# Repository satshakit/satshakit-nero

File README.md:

<h1 style="font-family: courier;" align="center"> satshakit-nero</h1>
<p align="center">

<div align="center"><i>An improved & fabbable multi-mcu flight controller board.</i></div>
</p>  

What is satshakit?
--

satshakit is a **Arduino IDE  and libraries compatible**, fabbable and open source board.

Here you can find all of the satshakit boards: **[satshakit organization](https://github.com/satshakit)**.

satshakit-nero
--

**satshakit-nero** is microcontroller board designed around the **ATMega1284P** and the **ATMega328P** chips and it is suitable for advanced drone applications and scenarios in which it is needed to have two available microcontrollers. The ATMega328P manages the flight with the **[Multiwii](http://www.multiwii.com/)** while the ATMega1284P can be used to inject and override the transmitter stick values (ROLL, PITCH, YAW and THROTTLE) or to manage a set of additional sensors. In the board there is a jumper to enable or disable the serial communication between the two microcontrollers (SERIAL_COMMON in the Eagle board).

The ATMega328P microntroller gives to this board all the features of the original **[satshakit flight controller board](https://github.com/satshakit/satshakit-flight-controller)**:

- support for [any drone configuration](http://www.multiwii.com/connecting-elements) up to **8 motors**
- support for up to **6 channels** receivers 
- **16mhz crystal** for precise clock, reliability and compatibility
- possibility to connect and use **any IMU working at 5V** 

And plus it adds the features of the **[satshakit-128](https://github.com/satshakit/satshakit-128)**:

- **128k** flash memory
- **2 serials**
- **16k of ram**
- **32 IO** pins

Here you can have a look on **satshakit-nero board**:

**downloads (right click, download as)**

- [satshakit-nero eagle schematic](https://raw.githubusercontent.com/satshakit/satshakit-nero/master/eagle/satshakit-nero/satshakit-nero.sch)
- [satshakit-nero eagle board](https://raw.githubusercontent.com/satshakit/satshakit-nero/master/eagle/satshakit-nero/satshakit-nero.brd)
- [satshakit-nero inside cut png](https://raw.githubusercontent.com/satshakit/satshakit-nero/master/media/satshakit-nero-inside.png)
- [satshakit-nero outsite cut png](https://raw.githubusercontent.com/satshakit/satshakit-nero/master/media/satshakit-nero-outside.png)

**media**

satshakit-nero flying test:

Authors
--

- Daniele Ingrassia

Contact
--

- **ingrassiada@gmail.com**
- **[linkedin](http://it.linkedin.com/in/danieleingrassia)**

Thanks
--

[Aldo Sollazzo and Noumena.io](http://noumena.io/)

[Fablab Kamp-Lintfort](http://fablab.hochschule-rhein-waal.de/index.php/de/)<br />
Hochschule Rhein-Waal<br />
Friedrich-Heinrich-Allee 25, 47475 Kamp-Lintfort, Germany<br />
fablab@hochschule-rhein-waal.de

License
--
This work is licensed under the terms of the open source license: Creative Commons Attribution-ShareAlike 4.0 International ([CC BY-SA 4.0](https://creativecommons.org/licenses/by-sa/4.0/)).

Disclaimer  
--

<div class="align-justify">
This hardware/software is provided "as is", and you use the hardware/software at your own risk. Under no circumstances shall any author be liable for direct, indirect, special, incidental, or consequential damages resulting from the use, misuse, or inability to use this hardware/software, even if the authors have been advised of the possibility of such damages.</div>

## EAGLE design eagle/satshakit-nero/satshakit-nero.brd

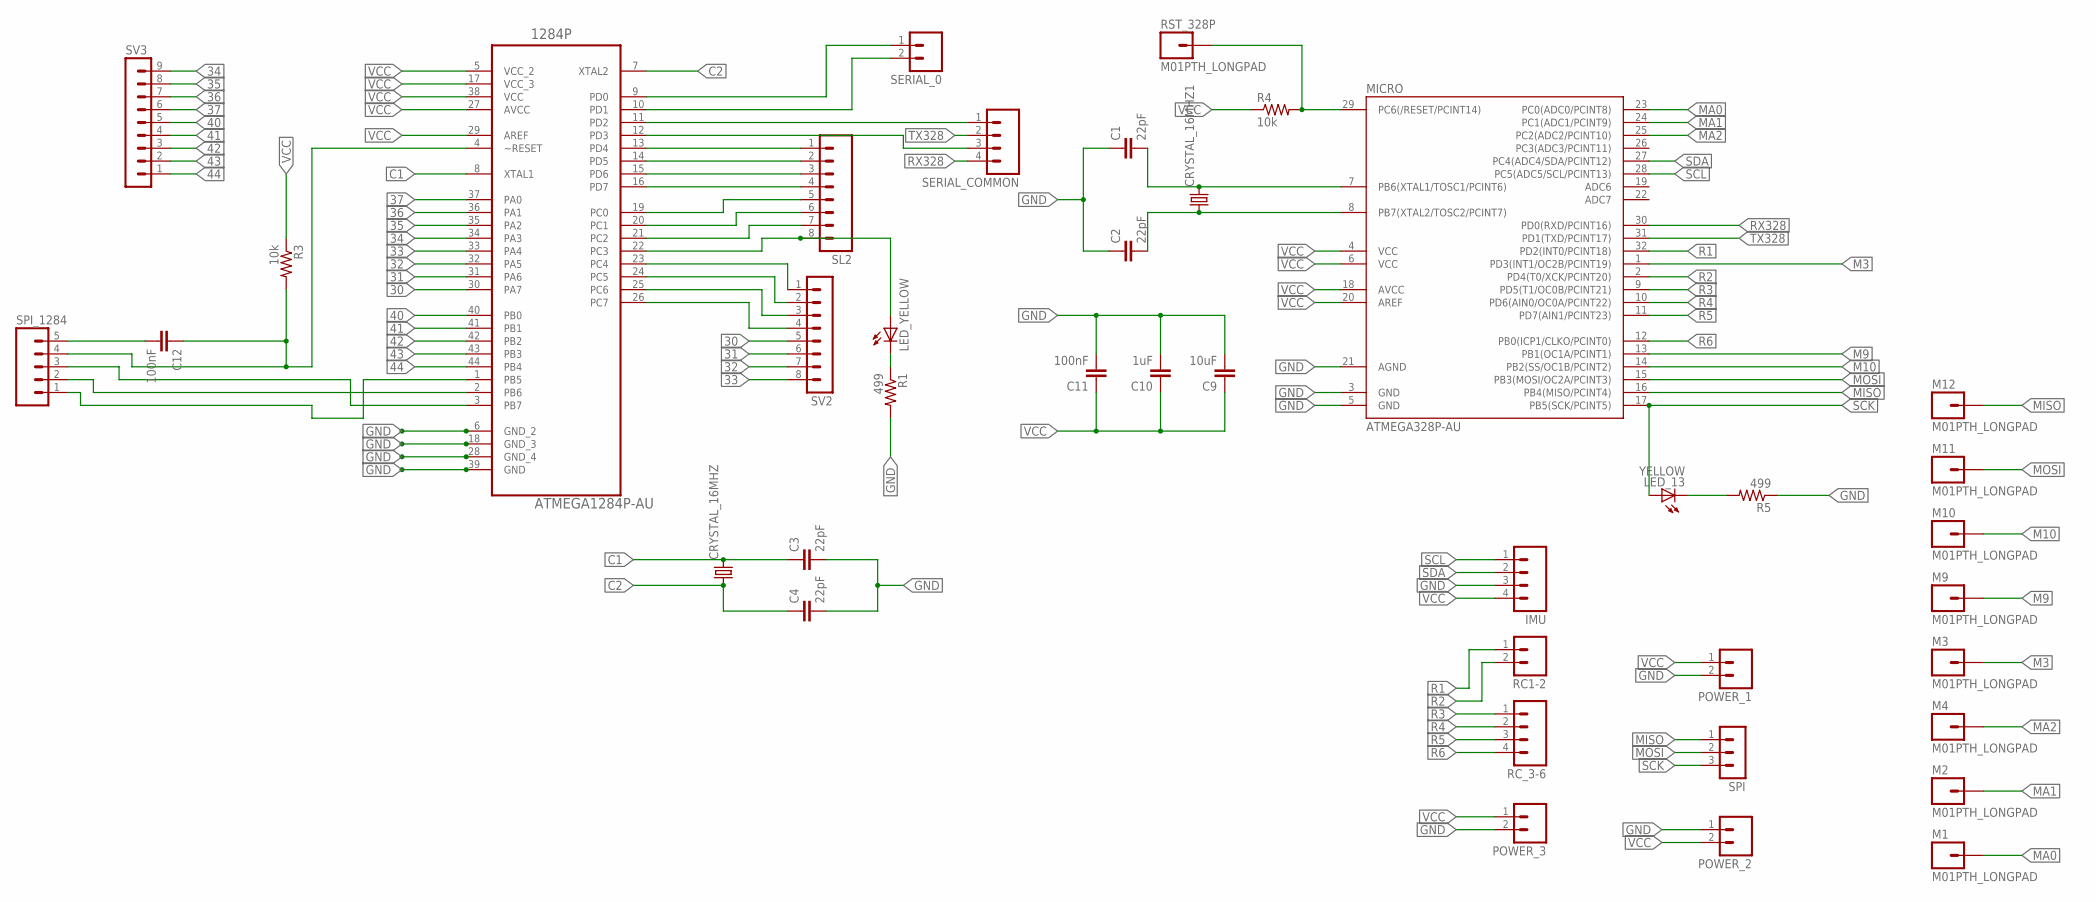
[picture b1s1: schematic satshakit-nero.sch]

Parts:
1284P: ATMEGA1284P-AU; QFP80P1200X1200X120-44N
C1, C2, C3, C4: 22pF; 1206
C9: 10uF; 1206
C10: 1uF; 1206
C11, C12: 100nF; 1206
CRYSTAL_16MHZ, CRYSTAL_16MHZ1: CRYSTALHC49UP; HC49UP
IMU: M04; 04P
LED_13: YELLOW; 1206
LED_YELLOW: LED1206; 1206
M1, M2, M3, M4, M9, M10, M11, M12: M01PTH_LONGPAD; 1X01_LONGPAD
MICRO: ATMEGA328P-AU; TQFP32-08
POWER_1, POWER_2, POWER_3: M02; 02P
R1: 499; R1206
R3: 10k; R1206
R4: 10k; 1206
R5: 499; 1206
RC1-2: M02; 02P
RC_3-6: M04LONGPADS; 1X04_LONGPADS
RST_328P: M01PTH_LONGPAD; 1X01_LONGPAD
SERIAL_0: M02; 02P
SERIAL_COMMON: M04; 04P
SL2: M08; 08P
SPI: MA03-1
SPI_1284: M05; 05P
SV2: MA08-1
SV3: MA09-1

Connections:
30: 1284P.30 (PA7), SV2.5
31: 1284P.31 (PA6), SV2.6
32: 1284P.32 (PA5), SV2.7
33: 1284P.33 (PA4), SV2.8
34: 1284P.34 (PA3), SV3.9
35: 1284P.35 (PA2), SV3.8
36: 1284P.36 (PA1), SV3.7
37: 1284P.37 (PA0), SV3.6
40: 1284P.40 (PB0), SV3.5
41: 1284P.41 (PB1), SV3.4
42: 1284P.42 (PB2), SV3.3
43: 1284P.43 (PB3), SV3.2
44: 1284P.44 (PB4), SV3.1
C1: 1284P.8 (XTAL1), C3.1, CRYSTAL_16MHZ.2
C2: 1284P.7 (XTAL2), C4.1, CRYSTAL_16MHZ.1
GND: 1284P.6 (GND_2), C1.1, C2.1, C3.2, C4.2, C9.2, C10.2, C11.2, IMU.3, MICRO.3 (GND), MICRO.5 (GND), MICRO.21 (AGND), POWER_1.2, POWER_2.1, POWER_3.2, R1.2, R5.1
M3: M3.1, MICRO.1 (PD3(INT1/OC2B/PCINT19))
M9: M9.1, MICRO.13 (PB1(OC1A/PCINT1))
M10: M10.1, MICRO.14 (PB2(SS/OC1B/PCINT2))
MA0: M1.1, MICRO.23 (PC0(ADC0/PCINT8))
MA1: M2.1, MICRO.24 (PC1(ADC1/PCINT9))
MA2: M4.1, MICRO.25 (PC2(ADC2/PCINT10))
MISO: M12.1, MICRO.16 (PB4(MISO/PCINT4)), SPI.1
MOSI: M11.1, MICRO.15 (PB3(MOSI/OC2A/PCINT3)), SPI.2
unnamed: 1284P.19 (PC0), SL2.5
unnamed: 1284P.20 (PC1), SL2.6
unnamed: 1284P.16 (PD7), SL2.4
unnamed: 1284P.14 (PD5), SL2.2
unnamed: 1284P.13 (PD4), SL2.1
unnamed: 1284P.12 (PD3), SERIAL_COMMON.3
unnamed: 1284P.11 (PD2), SERIAL_COMMON.1
unnamed: 1284P.9 (PD0), SERIAL_0.1
unnamed: 1284P.10 (PD1), SERIAL_0.2
unnamed: 1284P.21 (PC2), SL2.7
unnamed: 1284P.22 (PC3), LED_YELLOW.1 (A), SL2.8
unnamed: 1284P.23 (PC4), SV2.1
unnamed: 1284P.24 (PC5), SV2.2
unnamed: 1284P.25 (PC6), SV2.3
unnamed: 1284P.26 (PC7), SV2.4
unnamed: 1284P.15 (PD6), SL2.3
unnamed: 1284P.3 (PB7), SPI_1284.3
unnamed: 1284P.2 (PB6), SPI_1284.2
unnamed: 1284P.1 (PB5), SPI_1284.1
unnamed: 1284P.4 (~RESET), C12.1, R3.2, SPI_1284.4
unnamed: LED_YELLOW.2 (C), R1.1
unnamed: C12.2, SPI_1284.5
unnamed: C1.2, CRYSTAL_16MHZ1.2, MICRO.7 (PB6(XTAL1/TOSC1/PCINT6))
unnamed: C2.2, CRYSTAL_16MHZ1.1, MICRO.8 (PB7(XTAL2/TOSC2/PCINT7))
unnamed: MICRO.29 (PC6(/RESET/PCINT14)), R4.2, RST_328P.1
unnamed: LED_13.2 (C), R5.2
R1: MICRO.32 (PD2(INT0/PCINT18)), RC1-2.1
R2: MICRO.2 (PD4(T0/XCK/PCINT20)), RC1-2.2
R3: MICRO.9 (PD5(T1/OC0B/PCINT21)), RC_3-6.1
R4: MICRO.10 (PD6(AIN0/OC0A/PCINT22)), RC_3-6.2
R5: MICRO.11 (PD7(AIN1/PCINT23)), RC_3-6.3
R6: MICRO.12 (PB0(ICP1/CLKO/PCINT0)), RC_3-6.4
RX328: MICRO.30 (PD0(RXD/PCINT16)), SERIAL_COMMON.4
SCK: LED_13.1 (A), MICRO.17 (PB5(SCK/PCINT5)), SPI.3
SCL: IMU.1, MICRO.28 (PC5(ADC5/SCL/PCINT13))
SDA: IMU.2, MICRO.27 (PC4(ADC4/SDA/PCINT12))
TX328: MICRO.31 (PD1(TXD/PCINT17)), SERIAL_COMMON.2
VCC: 1284P.5 (VCC_2), 1284P.17 (VCC_3), 1284P.27 (AVCC), 1284P.29 (AREF), C9.1, C10.1, C11.1, IMU.4, MICRO.4 (VCC), MICRO.6 (VCC), MICRO.18 (AVCC), MICRO.20 (AREF), POWER_1.1, POWER_2.2, POWER_3.1, R3.1, R4.1

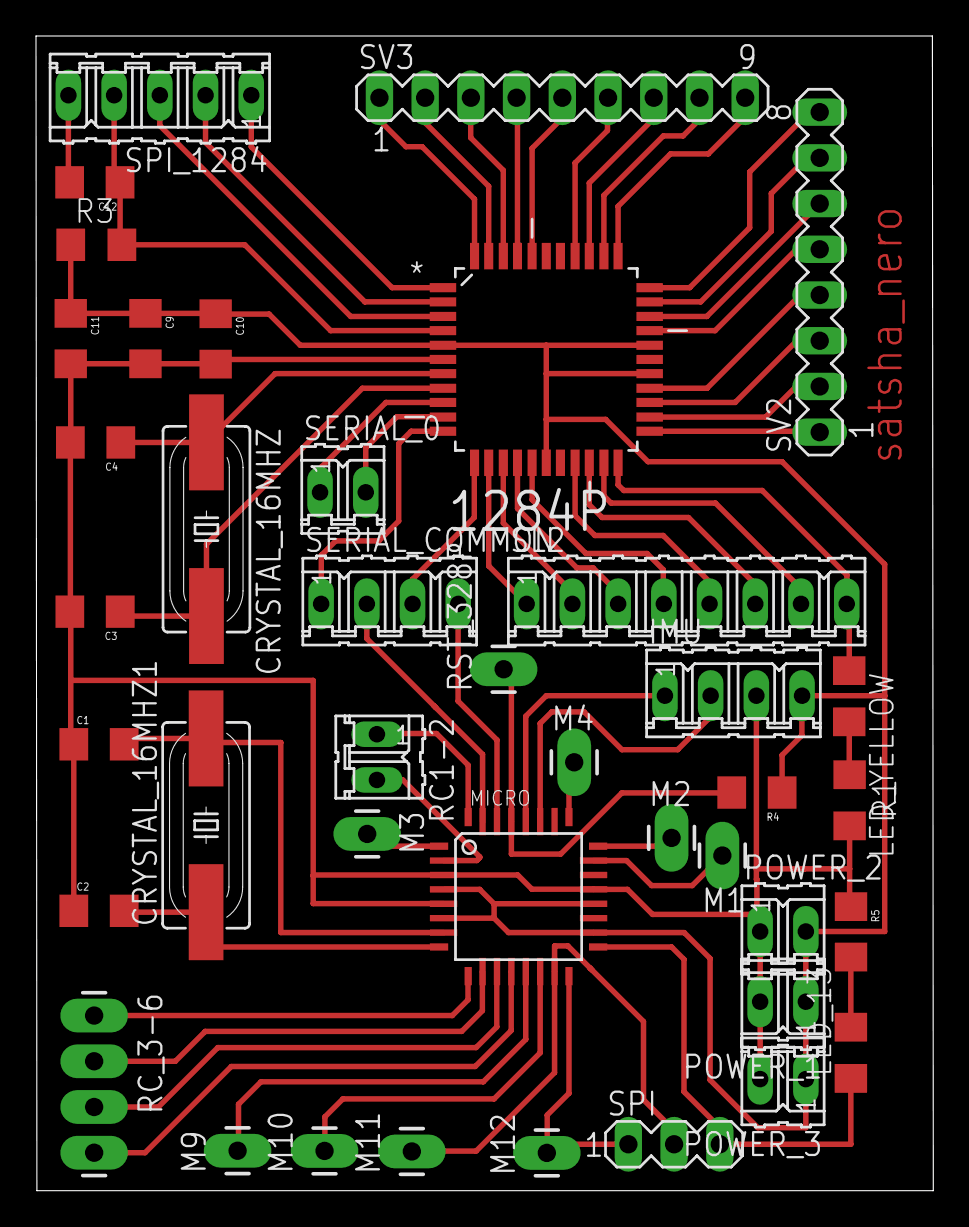
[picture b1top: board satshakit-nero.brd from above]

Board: 2 copper layers, 49.8 x 64.1 mm, 40 parts (0 on the bottom side), 62 nets.

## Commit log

2017-10-17 added eagle boards and media
2017-10-17 fixed readme first image
2017-10-17 added download links
2017-10-17 added specs and fixed readme
2017-10-17 readme fixes
2020-05-31 license change

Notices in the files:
parts and their libraries:
01_SparkFun: Licensing: CC v3.0 Share-Alike You are welcome to use this library for commercial purposes.
